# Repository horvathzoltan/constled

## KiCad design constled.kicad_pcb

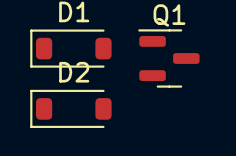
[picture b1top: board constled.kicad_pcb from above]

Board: 2 copper layers, 3 parts (0 on the bottom side), 2 nets, no tracks yet.

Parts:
D1, D2: 1N4148W; D_SOD-123
Q1: BC817; SOT-23

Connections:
unnamed: D1.2 (A), Q1.1 (B)
unnamed: D1.1 (K), D2.2 (A)
